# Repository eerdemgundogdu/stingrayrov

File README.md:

# Stingray ROV

CU AVTECH su alti takimi tarafindan TEKNOFEST icin gelistirilen 6 iticili su alti aracinin (ROV) kontrol yazilimi ve tasiyici kart tasarimi. Proje Kritik Tasarim Raporu (KTR) asamasini gecmistir.

Sistem iki katmandan olusur:

- Teensy 4.1 (`teensy/`): ESC PWM surusu, IMU ve analog sensor okumalari, donanimsal/yazilimsal emniyet kilitleri.
- Jetson Orin Nano (`jetson/`): ROS 2 tabanli durum kestirimi (EKF ve derinlik Kalman filtresi), derinlik/yaw PID kontrolculeri, su alti goruntu isleme ve gorev durum makinesi.

## Teensy 4.1 Firmware (`teensy/`)

Ayni surucu katmanini (`stingray_teensy/`) kullanan iki farkli zamanlama yapisi vardir:

- `freertos` ve `freertos_carrier`: 5 oncelikli FreeRTOS gorevi (1 kHz kontrol, 1 kHz IMU, 1 kHz RX / 50 Hz TX seri haberlesme, 100 Hz basinc/batarya/sizinti okuma, 10 Hz izleme). Paylasilan durum ve ADC erisimi mutex korumali calisir; donanim watchdog yalnizca tum gorevler olay grubuna (event group) bit bildirdiginde beslenir.
- `superloop` ve `superloop_carrier`: Zaman dilimli tek dongu (`stingray_teensy.ino`).

Surucu ve sinyal isleme detaylari:

- Motor surucusu (`motor_driver.cpp`, `frame_codec.cpp`): 6x ESC PWM cikisi (1100-1900 us, 1500 us notr). Ani akim sicramalarini ve mekanik darbe momentini sinirlamak icin 20 us/ms degisim hizi sinirlayicisi (slew-rate limiter) ve +-12 us notr olu bolge uygulanir.
- IMU (`imu_sensor.cpp`, `dsp_filter.cpp`): 400 kHz I2C uzerinden MPU6050 okunur. 1 kHz yaw hizi kanalinda fircasiz iticilerin olusturdugu 120 Hz govde titresimini bastirmak icin 2. derece IIR Biquad centik (notch) filtre ve 35 Hz Butterworth alcak geciren filtre kaskadi kullanilir.
- Basinc / derinlik (`depth_sensor.cpp`): 0-1.6 MPa ratiometric basinc sensoru (SEN0257) 5-orneklik kayan medyan + EMA filtresinden gecirilerek hidrostatik derinlige cevrilir.
- Seri protokol (`frame_codec.cpp`): CRC-8 (polinom 0x07) korumali sabit uzunluklu ikili cerceveler (15 bayt komut `0xAA 0x55`, 16 bayt telemetri `0xBB 0x66`). Kayan pencereli ayristirici bozuk baytlardan sonra senkronizasyonu kaybetmeden devam eder.
- Emniyet (`safety_monitor.cpp`): 500 ms icinde gecerli paket gelmezse motorlar notre cekilir. Rev A tasiyici kartta (`CARRIER_BOARD_REV=1`) manyetik kill-switch (`Pin 36`), ESC kontaktor surucusu (`Pin 38`) ve su sizintisi durumunda acil satiha cikis mantigi bulunur.

## Jetson ROS 2 Paketi (`jetson/src/`)

- `serial_bridge_node`: Teensy ile USB seri hat uzerinden ikili cerceve alisverisi.
- `sensor_node`: Basinc sifirlama kalibrasyonu, `[derinlik, dikey hiz]` uzerinde 2 durumlu Kalman filtresi (`depth_filter.py`) ve `[x, y, u, v, yaw, gyro_bias]` uzerinde kuadratik hidrodinamik suruklenme modelli 6 durumlu su alti EKF (`ekf_navigation.py`).
- `controller_node`: 50 Hz derinlik ve yaw PID kontrolculeri (anti-windup ve Kalman hiz tureviyle) ve 45 derece X-konfigurasyonlu 6 itici dagitim matrisi.
- `vision_node`: Su alti kirmizi kanal zayiflamasi icin Gray-World renk dengesi, LAB uzayinda CLAHE kontrast iyilestirme, kapi/samandira aci-mesafe kestirimi ve boru hatti takibi (`vision_pipeline.py`).
- `mission_node` ve `safety_node`: Gorev durum makinesi ve derinlik/pil/sizinti denetimi.

## Tasiyici Kart (`hardware/`)

Teensy 4.1 ve su alti sensor/ESC baglantilari icin 2 katmanli KiCad PCB tasarimi (Rev A, 110x85 mm):

- 6S Li-Po giris korumasi (`F1` 1 A sigorta, `D1` SS16 ters polarite diyodu, `D2` SMBJ30CA TVS, `C1` 47 uF).
- `LMR16006X` (700 kHz, 5 V buck) ve `AP2112K-3.3` (3.3 V sensor LDO), `D4` (B5819W) USB/VIN izolasyonu.
- 6x ESC PWM konnektoru (`J5..J10`, BEC pini bos birakilarak toprak dongusu onlenir, 220 ohm seri + 100k pull-down).
- 5 V basinc sensoru gerilim bolucusu ve `BAT54S` klempi (`J2`), 400 kHz I2C MPU6050 hatti (`J3`), su sizinti probu (`J4`) ve 68k/10k 6S batarya ADC bolucusu.
- Su gecirmez NC manyetik kill-switch (`J11`) ile seri bagli ana itici kontaktor bobini (`J12`, `Q2` BCP56-16).

Tasarim hesaplari `hardware/DESIGN.md`, konnektor tablolari `hardware/WIRING.md`, uretim dosyalari (Gerber, BOM, CPL, sematik PDF) `hardware/output/` altindadir.

## Derleme ve Testler

Donanim veya ROS kurulumu olmadan calisan C++ ve Python birim testleri:

```bash
cmake -S teensy/test -B build/test && cmake --build build/test && ctest --test-dir build/test --output-on-failure

python3 jetson/test/test_protocol.py
python3 jetson/test/test_depth_filter.py
python3 jetson/test/test_ekf_navigation.py
python3 jetson/test/test_vision.py
python3 jetson/test/test_controller.py
```

Teensy derlemesi:

```bash
cd teensy
pio run -e freertos
pio run -e freertos_carrier
pio run -e superloop
pio run -e superloop_carrier
```

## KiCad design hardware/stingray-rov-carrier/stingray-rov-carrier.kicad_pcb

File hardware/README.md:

# Stingray ROV Tasiyici Kart (Rev A)

Teensy 4.1 tabanli 6 iticili ROV icin 2 katmanli (110x85 mm, FR-4, 1.6 mm, 1 oz bakir) tasiyici PCB tasarimi.

| Ust yuz | Izometrik |
| --- | --- |
|  |  |

| Alt yuz (GND dokumu) | Bakir + silkscreen yerlesimi |
| --- | --- |
|  |  |

Gorseller KiCad 9 3B goruntuleyicisinden (`kicad-cli pcb render`) uretilmistir; Teensy 4.1 soketi icin 3B model olmadigindan sadece header pedleri gorunur.

Kartin cozdugu temel elektriksel noktalar:

- 6S Li-Po (22.2 V nominal, 25.2 V tam dolu) girisinde 1 A sigorta (`F1`), SS16 ters polarite diyodu (`D1`), SMBJ30CA TVS (`D2`) ve 47 uF giris kondansatoru (`C1`).
- 6S hattan 5 V uretimi icin `LMR16006X` (700 kHz, 0.6 A buck, `U1`) ve 3.3 V sensor beslemesi icin `AP2112K-3.3` LDO (`U2`). Jetson USB 5 V hatti ile kartin 5 V hatti `D4` (B5819W) ile ayrilir.
- 5 V cikisli SEN0257 basinc sensorunun 3.3 V toleransli Teensy ADC pinine (`Pin 16 / A2`) 10k/10k bolucu (`R21`, `R22`), 100 nF filtre (`C11`) ve `BAT54S` Schottky klempi (`D6`) ile baglanmasi.
- 6x ESC PWM cikisinda (`J5..J10`) ESC BEC +5 V pininin bos birakilmasi, 220 ohm seri direnc ve MCU reset sirasinda ESC'leri sessiz tutan 100k pull-down.
- Disaridan mudahale edilebilen su gecirmez NC manyetik kill-switch (`J11`) ile ana itici guc kontaktoru bobininin (`J12`) seri baglanmasi. Miknatis cekildiginde kontaktor yazilimdan bagimsiz olarak duser; Teensy `T_KILL_SENSE` (`Pin 36`) ile durumu okur ve `T_ESC_EN` (`Pin 38`, `Q2` BCP56-16) ile kontaktoru acip kapatabilir.

## Dizin Yapisi

- `DESIGN.md`: Devre hesaplari, filtre ve bolucu secimleri, PCB kurallari.
- `WIRING.md`: Konnektor ve Teensy 4.1 pin eslemesi.
- `stingray-rov-carrier/`: KiCad proje, sematik ve PCB dosyalari.
- `output/`: Gerber + delik paketi, BOM, CPL (pick-and-place), sematik PDF ve DRC raporu.
- `gen/`: Tek kaynak netlist (`design.py`) uzerinden sematik ve PCB'yi ureten Python betikleri.

Yeniden uretmek icin:

```bash
cd hardware/gen
python3 build.py
```

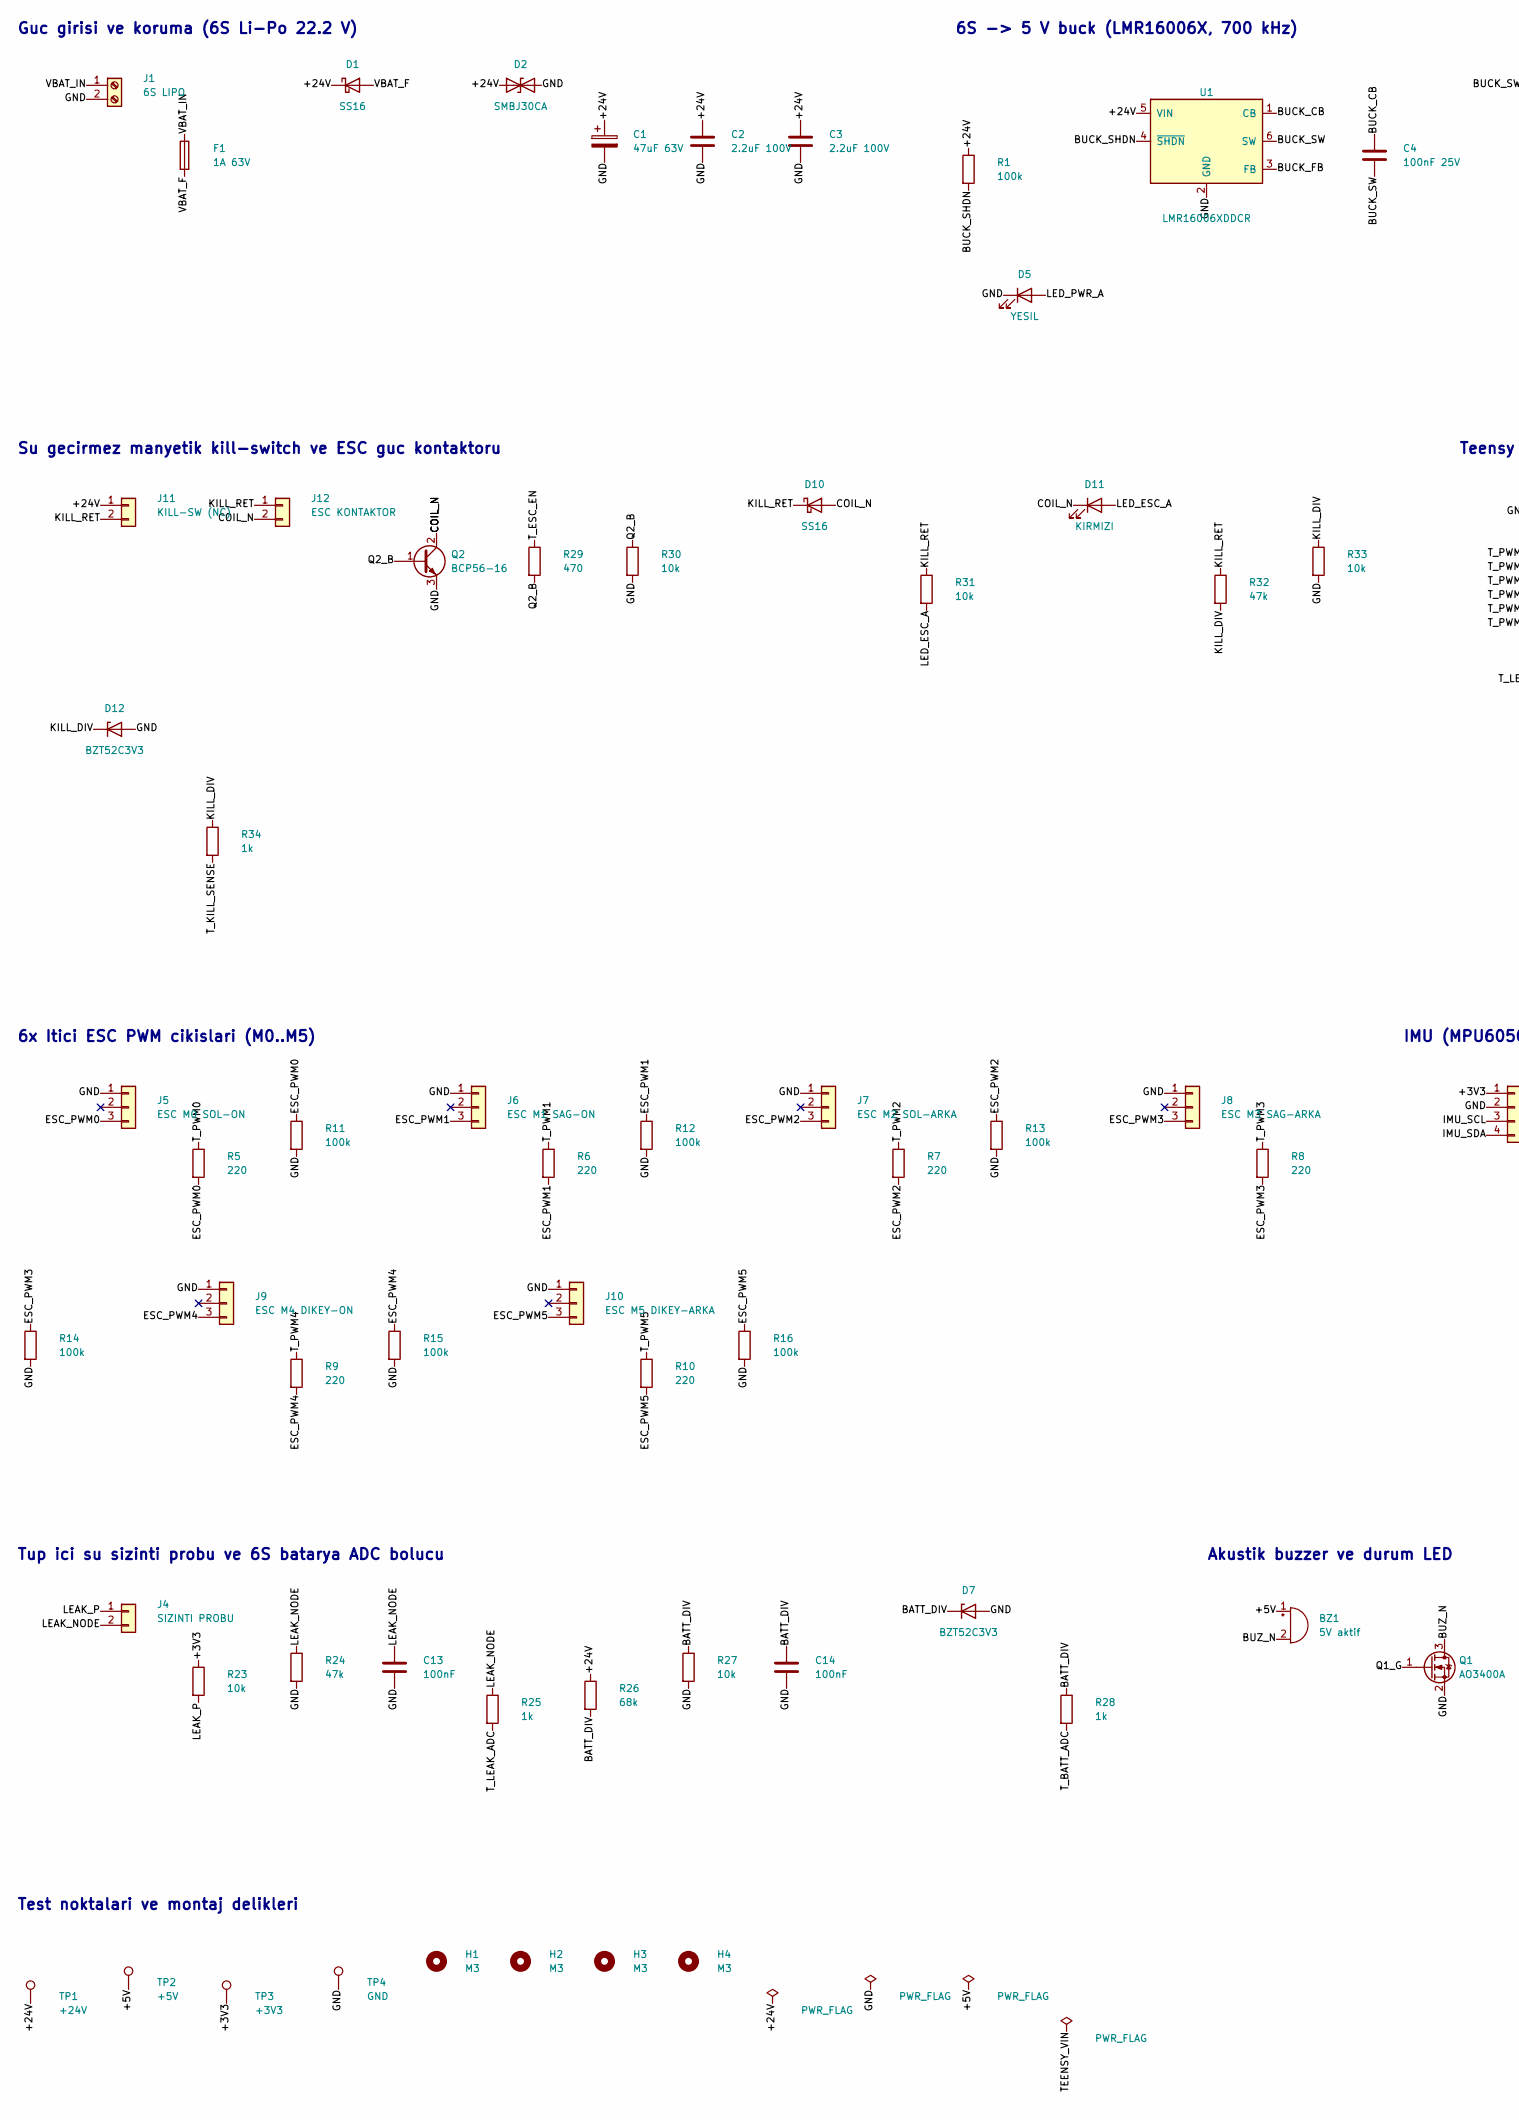
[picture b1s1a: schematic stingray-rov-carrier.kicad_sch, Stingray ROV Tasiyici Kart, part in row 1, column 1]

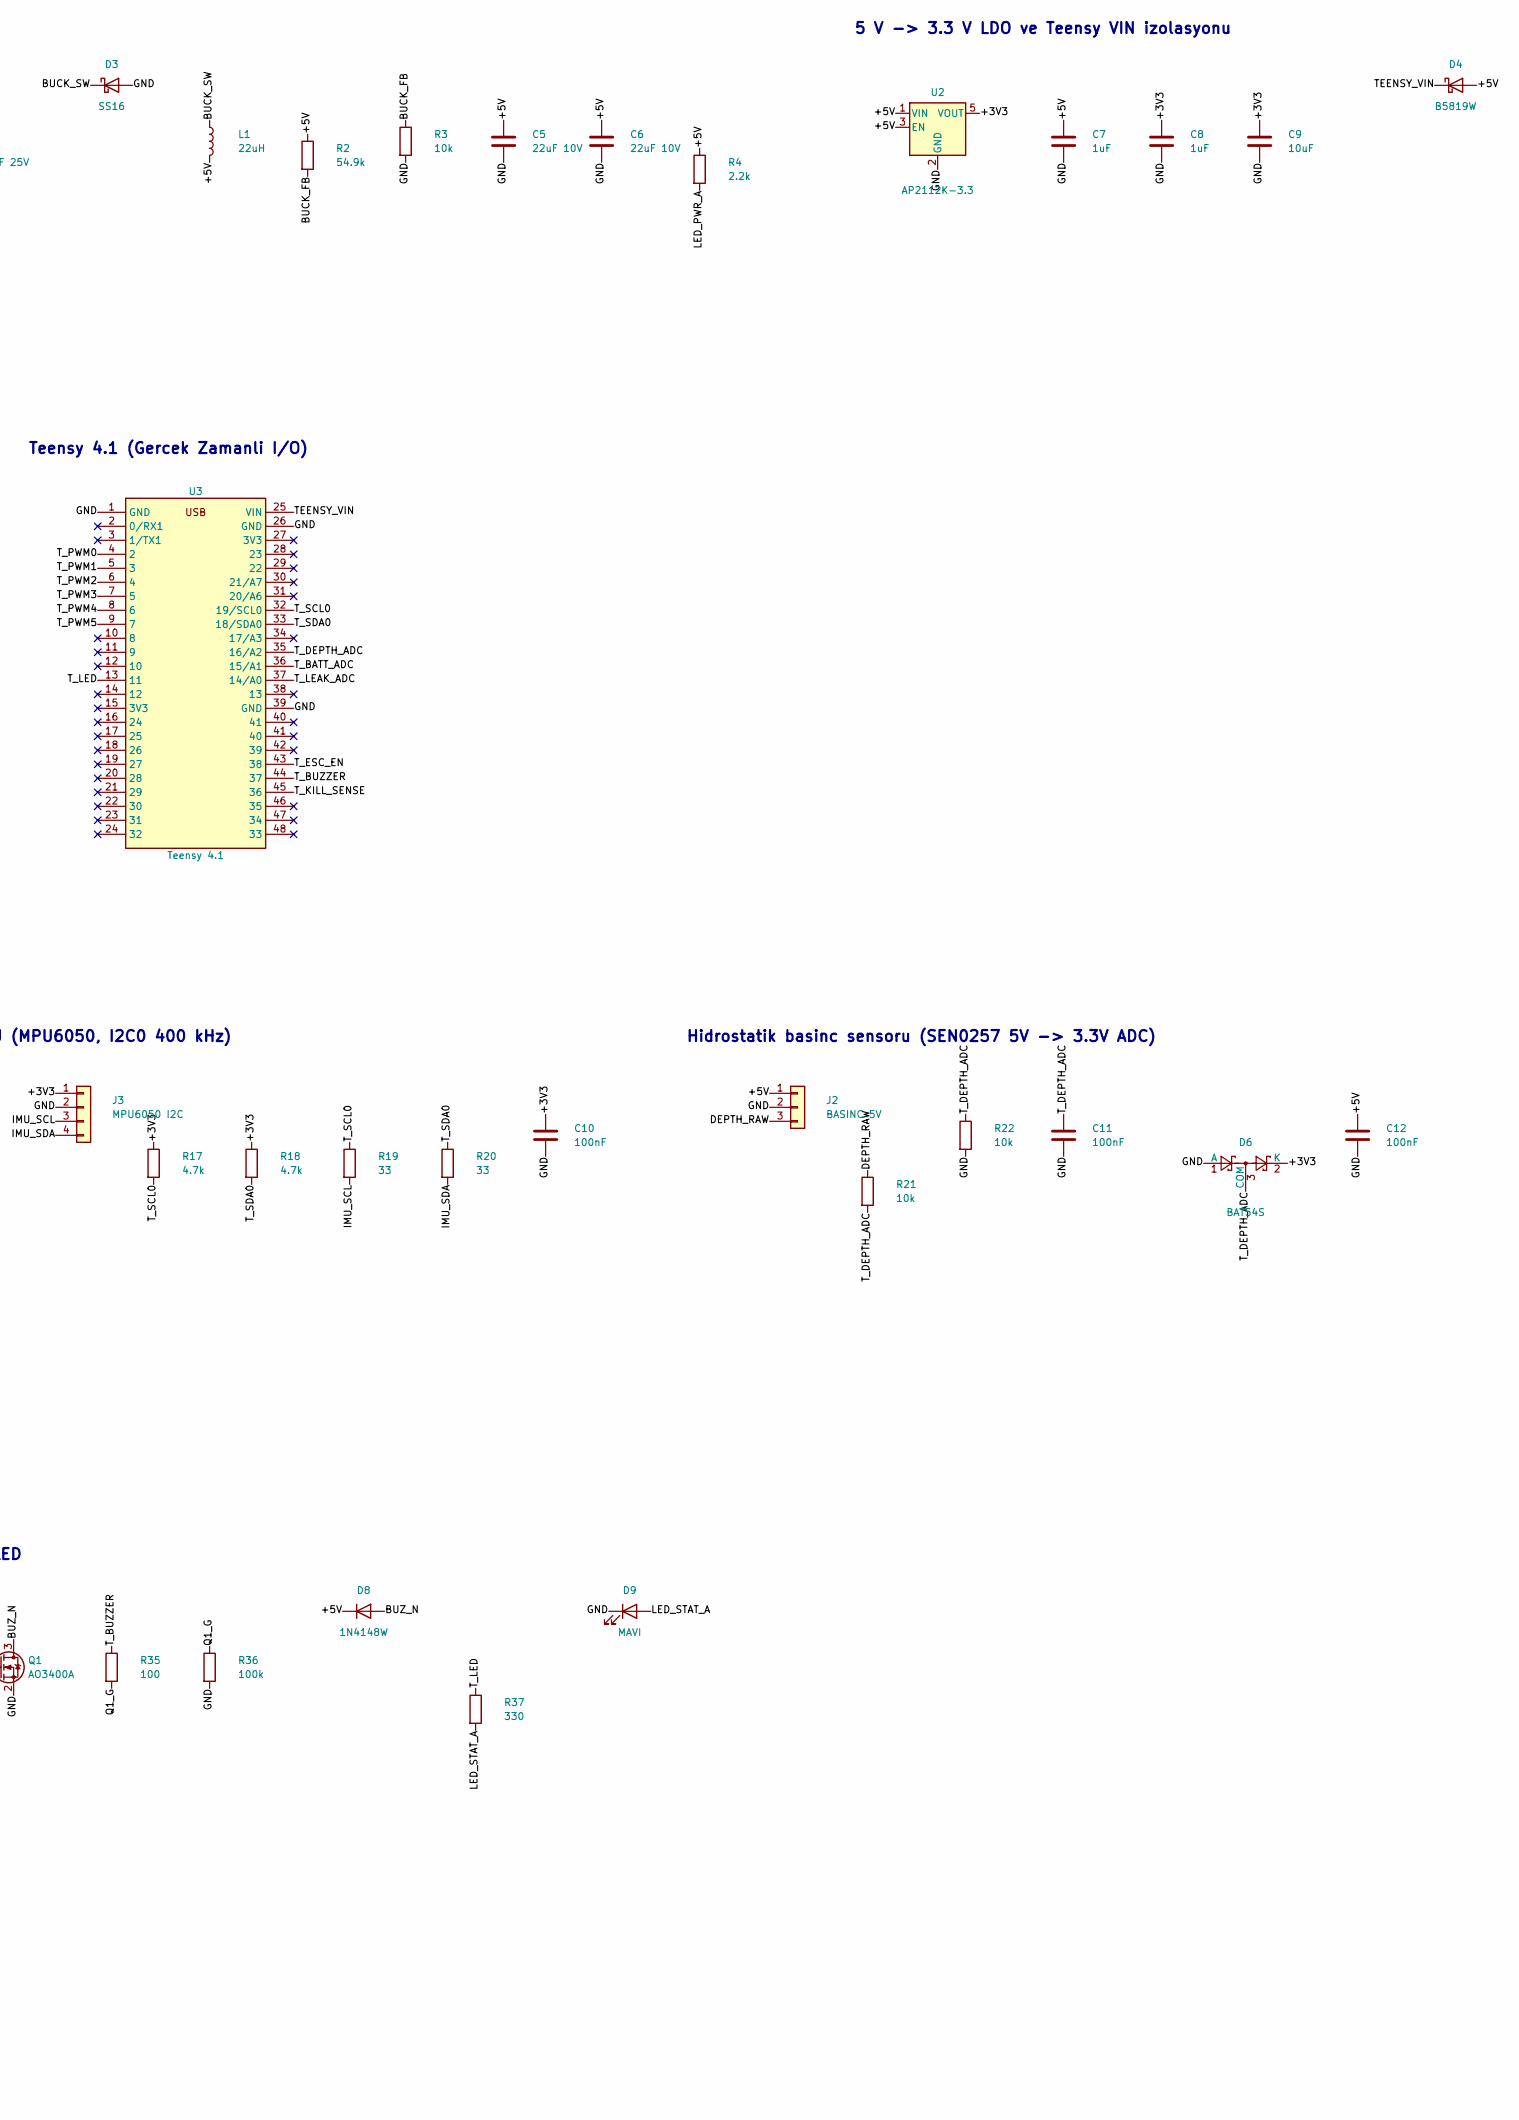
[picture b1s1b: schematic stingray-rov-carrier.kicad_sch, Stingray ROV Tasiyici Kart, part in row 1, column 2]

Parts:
BZ1: 5V aktif; Buzzer_12x9.5RM7.6; MPN 12 mm 5V aktif buzzer
C1: 47uF 63V; CP_Elec_8x10; MPN Panasonic EEE-FK1J470P
C2, C3: 2.2uF 100V; C_1210_3225Metric; MPN X7R 1210 100V
C4: 100nF 25V; C_0603_1608Metric; MPN X7R 0603 25V
C5, C6: 22uF 10V; C_1206_3216Metric; MPN X7R 1206 10V
C7, C8: 1uF; C_0603_1608Metric; MPN X7R 0603 16V
C9: 10uF; C_0805_2012Metric; MPN X5R 0805 10V
C10, C11, C12, C13, C14: 100nF; C_0603_1608Metric; MPN X7R 0603 16V
D1, D3, D10: SS16; D_SMA; MPN SS16 (60V 1A)
D2: SMBJ30CA; D_SMB; MPN Littelfuse SMBJ30CA
D4: B5819W; D_SOD-123; MPN B5819W (40V 1A)
D5: YESIL; LED_0603_1608Metric; MPN 0603 yesil LED
D6: BAT54S; SOT-23; MPN BAT54S
D7, D12: BZT52C3V3; D_SOD-123; MPN BZT52C3V3
D8: 1N4148W; D_SOD-323; MPN 1N4148WS
D9: MAVI; LED_0603_1608Metric; MPN 0603 mavi LED
D11: KIRMIZI; LED_0603_1608Metric; MPN 0603 kirmizi LED
F1: 1A 63V; Fuse_1206_3216Metric; MPN Littelfuse 0466001.NRHF
H1, H2, H3, H4: M3; MountingHole_3.2mm_M3
J1: 6S LIPO; TerminalBlock_Phoenix_MKDS-1,5-2-5.08_1x02_P5.08mm_Horizont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; MPN Phoenix 1715721
J2: BASINC 5V; JST_XH_B3B-XH-A_1x03_P2.50mm_Vertical; MPN JST B3B-XH-A
J3: MPU6050 I2C; JST_XH_B4B-XH-A_1x04_P2.50mm_Vertical; MPN JST B4B-XH-A
J4: SIZINTI PROBU; JST_XH_B2B-XH-A_1x02_P2.50mm_Vertical; MPN JST B2B-XH-A
J5: ESC M0 SOL-ON; JST_XH_B3B-XH-A_1x03_P2.50mm_Vertical; MPN JST B3B-XH-A
J6: ESC M1 SAG-ON; JST_XH_B3B-XH-A_1x03_P2.50mm_Vertical; MPN JST B3B-XH-A
J7: ESC M2 SOL-ARKA; JST_XH_B3B-XH-A_1x03_P2.50mm_Vertical; MPN JST B3B-XH-A
J8: ESC M3 SAG-ARKA; JST_XH_B3B-XH-A_1x03_P2.50mm_Vertical; MPN JST B3B-XH-A
J9: ESC M4 DIKEY-ON; JST_XH_B3B-XH-A_1x03_P2.50mm_Vertical; MPN JST B3B-XH-A
J10: ESC M5 DIKEY-ARKA; JST_XH_B3B-XH-A_1x03_P2.50mm_Vertical; MPN JST B3B-XH-A
J11: KILL-SW (NC); JST_XH_B2B-XH-A_1x02_P2.50mm_Vertical; MPN JST B2B-XH-A
J12: ESC KONTAKTOR; JST_XH_B2B-XH-A_1x02_P2.50mm_Vertical; MPN JST B2B-XH-A
L1: 22uH; L_Bourns_SRN6045TA; MPN Bourns SRN6045TA-220M
Q1: AO3400A; SOT-23; MPN AOS AO3400A
Q2: BCP56-16; SOT-223-3_TabPin2; MPN Nexperia BCP56-16
R1, R11, R12, R13, R14, R15, R16, R36: 100k; R_0603_1608Metric; MPN 0603 100k 1%
R2: 54.9k; R_0603_1608Metric; MPN 0603 54.9k 1%
R3, R21, R22, R23, R27, R30, R31, R33: 10k; R_0603_1608Metric; MPN 0603 10k 1%
R4: 2.2k; R_0603_1608Metric; MPN 0603 2.2k 1%
R5, R6, R7, R8, R9, R10: 220; R_0603_1608Metric; MPN 0603 220 1%
R17, R18: 4.7k; R_0603_1608Metric; MPN 0603 4.7k 1%
R19, R20: 33; R_0603_1608Metric; MPN 0603 33 1%
R24, R32: 47k; R_0603_1608Metric; MPN 0603 47k 1%
R25, R28, R34: 1k; R_0603_1608Metric; MPN 0603 1k 1%
R26: 68k; R_0603_1608Metric; MPN 0603 68k 1%
R29: 470; R_0603_1608Metric; MPN 0603 470 1%
R35: 100; R_0603_1608Metric; MPN 0603 100 1%
R37: 330; R_0603_1608Metric; MPN 0603 330 1%
TP1: +24V; TestPoint_Pad_D1.5mm
TP2: +5V; TestPoint_Pad_D1.5mm
TP3: +3V3; TestPoint_Pad_D1.5mm
TP4: GND; TestPoint_Pad_D1.5mm
U1: LMR16006XDDCR; SOT-23-6; MPN TI LMR16006XDDCR
U2: AP2112K-3.3; SOT-23-5; MPN Diodes AP2112K-3.3TRG1
U3: Teensy 4.1; Teensy4.1_Socket; MPN PJRC Teensy 4.1 + 2x 1x24 disi header

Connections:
+3V3: C8.1, C9.1, C10.1, D6.2 (K), J3.1, R17.1, R18.1, R23.1, TP3.1, U2.5 (VOUT)
+5V: BZ1.1 (+), C5.1, C6.1, C7.1, C12.1, D4.2 (A), D8.1 (K), J2.1, L1.2, R2.1, R4.1, TP2.1, U2.1 (VIN), U2.3 (EN)
+24V: C1.1, C2.1, C3.1, D1.1 (K), D2.1 (A1), J11.1, R1.1, R26.1, TP1.1, U1.5 (VIN)
BATT_DIV: C14.1, D7.1 (K), R26.2, R27.1, R28.1
BUCK_CB: C4.1, U1.1 (CB)
BUCK_FB: R2.2, R3.1, U1.3 (FB)
BUCK_SHDN: R1.2, U1.4 (~SHDN)
BUCK_SW: C4.2, D3.1 (K), L1.1, U1.6 (SW)
BUZ_N: BZ1.2 (-), D8.2 (A), Q1.3 (D)
COIL_N: D10.2 (A), D11.1 (K), J12.2, Q2.2 (C), Q2.4 (C)
DEPTH_RAW: J2.3, R21.1
ESC_PWM0: J5.3, R5.2, R11.1
ESC_PWM1: J6.3, R6.2, R12.1
ESC_PWM2: J7.3, R7.2, R13.1
ESC_PWM3: J8.3, R8.2, R14.1
ESC_PWM4: J9.3, R9.2, R15.1
ESC_PWM5: J10.3, R10.2, R16.1
GND: C1.2, C2.2, C3.2, C5.2, C6.2, C7.2, C8.2, C9.2, C10.2, C11.2, C12.2, C13.2, C14.2, D2.2 (A2), D3.2 (A), D5.1 (K), D6.1 (A), D7.2 (A), D9.1 (K), D12.2 (A), J1.2, J2.2, J3.2, J5.1, J6.1, J7.1, J8.1, J9.1, J10.1, Q1.2 (S), Q2.3 (E), R3.2, R11.2, R12.2, R13.2, R14.2, R15.2, R16.2, R22.2, R24.2, R27.2, R30.2, R33.2, R36.2, TP4.1, U1.2 (GND), U2.2 (GND), U3.1 (GND), U3.26 (GND), U3.39 (GND)
IMU_SCL: J3.3, R19.2
IMU_SDA: J3.4, R20.2
KILL_DIV: D12.1 (K), R32.2, R33.1, R34.1
KILL_RET: D10.1 (K), J11.2, J12.1, R31.1, R32.1
LEAK_NODE: C13.1, J4.2, R24.1, R25.1
LEAK_P: J4.1, R23.2
LED_ESC_A: D11.2 (A), R31.2
LED_PWR_A: D5.2 (A), R4.2
LED_STAT_A: D9.2 (A), R37.2
Q1_G: Q1.1 (G), R35.2, R36.1
Q2_B: Q2.1 (B), R29.2, R30.1
TEENSY_VIN: D4.1 (K), U3.25 (VIN)
T_BATT_ADC: R28.2, U3.36 (15/A1)
T_BUZZER: R35.1, U3.44 (37)
T_DEPTH_ADC: C11.1, D6.3 (COM), R21.2, R22.1, U3.35 (16/A2)
T_ESC_EN: R29.1, U3.43 (38)
T_KILL_SENSE: R34.2, U3.45 (36)
T_LEAK_ADC: R25.2, U3.37 (14/A0)
T_LED: R37.1, U3.13 (11)
T_PWM0: R5.1, U3.4 (2)
T_PWM1: R6.1, U3.5 (3)
T_PWM2: R7.1, U3.6 (4)
T_PWM3: R8.1, U3.7 (5)
T_PWM4: R9.1, U3.8 (6)
T_PWM5: R10.1, U3.9 (7)
T_SCL0: R17.2, R19.1, U3.32 (19/SCL0)
T_SDA0: R18.2, R20.1, U3.33 (18/SDA0)
VBAT_F: D1.2 (A), F1.2
VBAT_IN: F1.1, J1.1

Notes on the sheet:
Guc girisi ve koruma (6S Li-Po 22.2 V)
6S -> 5 V buck (LMR16006X, 700 kHz)
5 V -> 3.3 V LDO ve Teensy VIN izolasyonu
Su gecirmez manyetik kill-switch ve ESC guc kontaktoru
Teensy 4.1 (Gercek Zamanli I/O)
6x Itici ESC PWM cikislari (M0..M5)
IMU (MPU6050, I2C0 400 kHz)
Hidrostatik basinc sensoru (SEN0257 5V -> 3.3V ADC)
Tup ici su sizinti probu ve 6S batarya ADC bolucu
Akustik buzzer ve durum LED
Test noktalari ve montaj delikleri

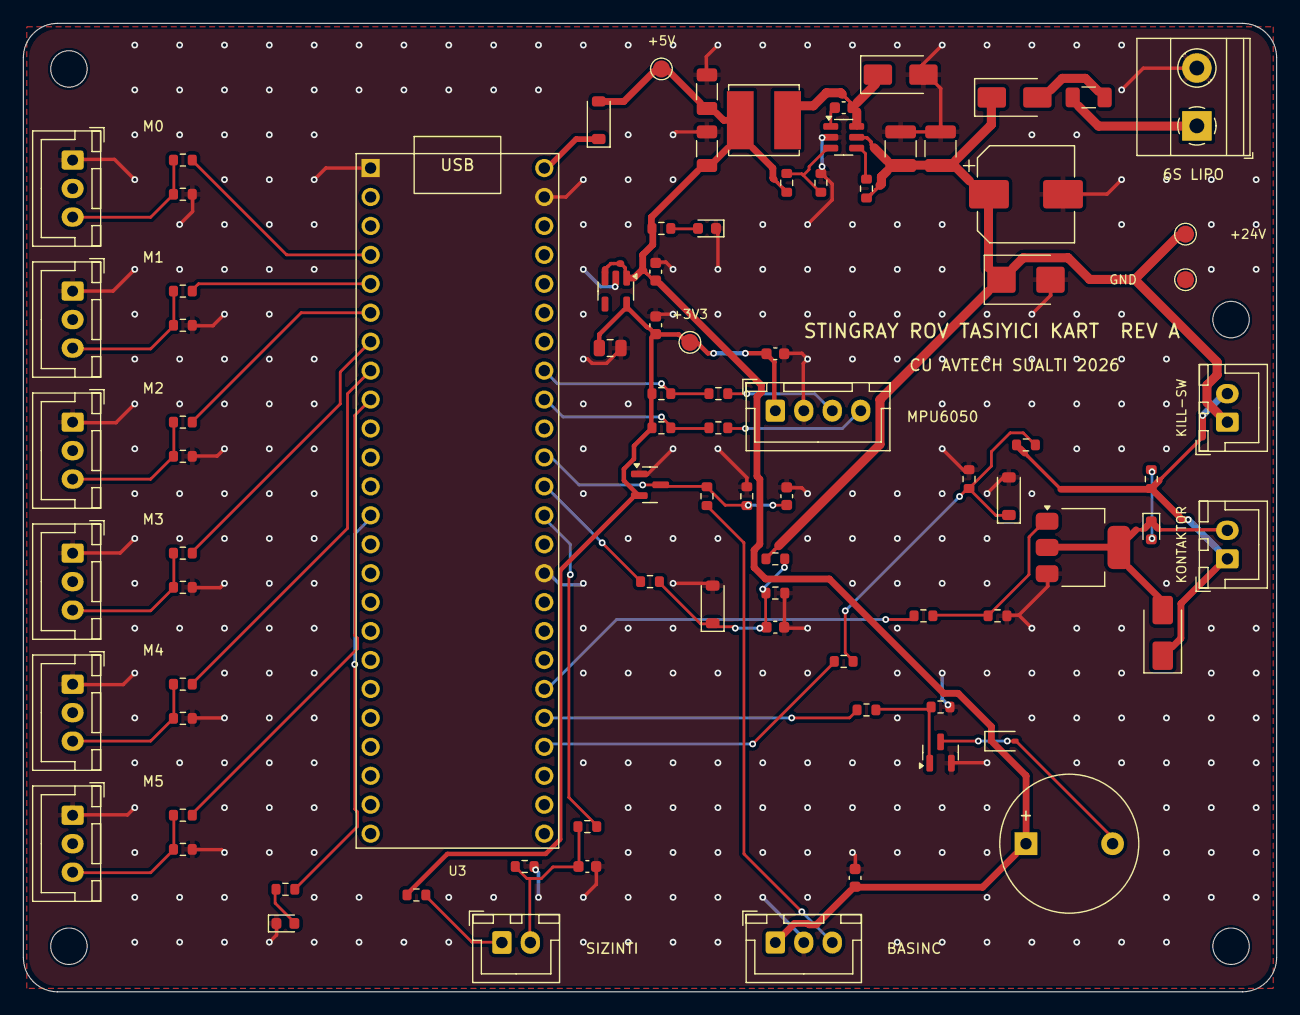
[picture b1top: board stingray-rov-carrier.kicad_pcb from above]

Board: 2 copper layers, 110.0 x 85.0 mm, 91 parts (0 on the bottom side), 47 nets.

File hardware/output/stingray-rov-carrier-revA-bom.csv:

Adet,Referanslar,Deger,Footprint,Parca,Not
1,BZ1,5V aktif,Buzzer_12x9.5RM7.6,12 mm 5V aktif buzzer,Tup ici arming / sizinti / dusuk pil sesli uyari
1,C1,47uF 63V,CP_Elec_8x10,Panasonic EEE-FK1J470P,Toplu giris kondansatoru (tether/aku kablosu rezonans sonumleme)
2,C2 C3,2.2uF 100V,C_1210_3225Metric,X7R 1210 100V,
1,C4,100nF 25V,C_0603_1608Metric,X7R 0603 25V,
2,C5 C6,22uF 10V,C_1206_3216Metric,X7R 1206 10V,
2,C7 C8,1uF,C_0603_1608Metric,X7R 0603 16V,
1,C9,10uF,C_0805_2012Metric,X5R 0805 10V,
5,C10 C11 C12 C13 C14,100nF,C_0603_1608Metric,X7R 0603 16V,
3,D1 D3 D10,SS16,D_SMA,SS16 (60V 1A),Bobin serbest gecis diyodu; Buck serbest gecis (catch) diyodu; Ters kutup korumasi
1,D2,SMBJ30CA,D_SMB,Littelfuse SMBJ30CA,Vrwm 30V; 6x ESC rejeneratif/enduktif sicrama kiskaci
1,D4,B5819W,D_SOD-123,B5819W (40V 1A),Jetson USB 5V ile kart 5V birbirini geri beslemesin
1,D5,YESIL,LED_0603_1608Metric,0603 yesil LED,+5V var
1,D6,BAT54S,SOT-23,BAT54S,Pin 16 (A2) asiri gerilim kiskaci
2,D7 D12,BZT52C3V3,D_SOD-123,BZT52C3V3,3.3 V kiskac; Batarya ADC 3.3 V kiskaci
1,D8,1N4148W,D_SOD-323,1N4148WS,Buzzer serbest gecis
1,D9,MAVI,LED_0603_1608Metric,0603 mavi LED,Durum LED (pin 11)
1,D11,KIRMIZI,LED_0603_1608Metric,0603 kirmizi LED,Itici ESC gucu acik
1,F1,1A 63V,Fuse_1206_3216Metric,Littelfuse 0466001.NRHF,Lojik + kontaktor bobini sigortasi
1,J1,6S LIPO,"TerminalBlock_Phoenix_MKDS-1,5-2-5.08_1x02_P5.08mm_Horizontal",Phoenix 1715721,"6S Li-Po girisi (ana sigortadan sonra, ESC kontaktorunden once)"
1,J2,BASINC 5V,JST_XH_B3B-XH-A_1x03_P2.50mm_Vertical,JST B3B-XH-A,"DFRobot SEN0257 (0.5-4.5V ratiometric, 1.6 MPa)"
1,J3,MPU6050 I2C,JST_XH_B4B-XH-A_1x04_P2.50mm_Vertical,JST B4B-XH-A,"Pin 18 SDA0, Pin 19 SCL0 @ 400 kHz"
1,J4,SIZINTI PROBU,JST_XH_B2B-XH-A_1x02_P2.50mm_Vertical,JST B2B-XH-A,Tup ici iletken su sizinti elektrotlari
1,J5,ESC M0 SOL-ON,JST_XH_B3B-XH-A_1x03_P2.50mm_Vertical,JST B3B-XH-A,Pin 2 (ESC BEC 5V) bilerek bagli degil
1,J6,ESC M1 SAG-ON,JST_XH_B3B-XH-A_1x03_P2.50mm_Vertical,JST B3B-XH-A,Pin 2 (ESC BEC 5V) bilerek bagli degil
1,J7,ESC M2 SOL-ARKA,JST_XH_B3B-XH-A_1x03_P2.50mm_Vertical,JST B3B-XH-A,Pin 2 (ESC BEC 5V) bilerek bagli degil
1,J8,ESC M3 SAG-ARKA,JST_XH_B3B-XH-A_1x03_P2.50mm_Vertical,JST B3B-XH-A,Pin 2 (ESC BEC 5V) bilerek bagli degil
1,J9,ESC M4 DIKEY-ON,JST_XH_B3B-XH-A_1x03_P2.50mm_Vertical,JST B3B-XH-A,Pin 2 (ESC BEC 5V) bilerek bagli degil
1,J10,ESC M5 DIKEY-ARKA,JST_XH_B3B-XH-A_1x03_P2.50mm_Vertical,JST B3B-XH-A,Pin 2 (ESC BEC 5V) bilerek bagli degil
1,J11,KILL-SW (NC),JST_XH_B2B-XH-A_1x02_P2.50mm_Vertical,JST B2B-XH-A,Su gecirmez manyetik acil durdurma anahtari (normalde kapali)
1,J12,ESC KONTAKTOR,JST_XH_B2B-XH-A_1x02_P2.50mm_Vertical,JST B2B-XH-A,"24V bobin, <= 0.4 A"
1,L1,22uH,L_Bourns_SRN6045TA,Bourns SRN6045TA-220M,Isat >= 1 A gerekli
1,Q1,AO3400A,SOT-23,AOS AO3400A,
1,Q2,BCP56-16,SOT-223-3_TabPin2,Nexperia BCP56-16,80V 1A; hFE 100-250
8,R1 R11 R12 R13 R14 R15 R16 R36,100k,R_0603_1608Metric,0603 100k 1%,
1,R2,54.9k,R_0603_1608Metric,0603 54.9k 1%,
8,R3 R21 R22 R23 R27 R30 R31 R33,10k,R_0603_1608Metric,0603 10k 1%,
1,R4,2.2k,R_0603_1608Metric,0603 2.2k 1%,
6,R5 R6 R7 R8 R9 R10,220,R_0603_1608Metric,0603 220 1%,
2,R17 R18,4.7k,R_0603_1608Metric,0603 4.7k 1%,
2,R19 R20,33,R_0603_1608Metric,0603 33 1%,
2,R24 R32,47k,R_0603_1608Metric,0603 47k 1%,
3,R25 R28 R34,1k,R_0603_1608Metric,0603 1k 1%,
1,R26,68k,R_0603_1608Metric,0603 68k 1%,
1,R29,470,R_0603_1608Metric,0603 470 1%,
1,R35,100,R_0603_1608Metric,0603 100 1%,
1,R37,330,R_0603_1608Metric,0603 330 1%,
1,U1,LMR16006XDDCR,SOT-23-6,TI LMR16006XDDCR,X versiyonu (700 kHz); sembol Y ile pin uyumlu
1,U2,AP2112K-3.3,SOT-23-5,Diodes AP2112K-3.3TRG1,600 mA; IMU + sizinti algilama hatti
1,U3,Teensy 4.1,Teensy4.1_Socket,PJRC Teensy 4.1 + 2x 1x24 disi header,Tum 3.3V pinleri bos; VIN D4 uzerinden
